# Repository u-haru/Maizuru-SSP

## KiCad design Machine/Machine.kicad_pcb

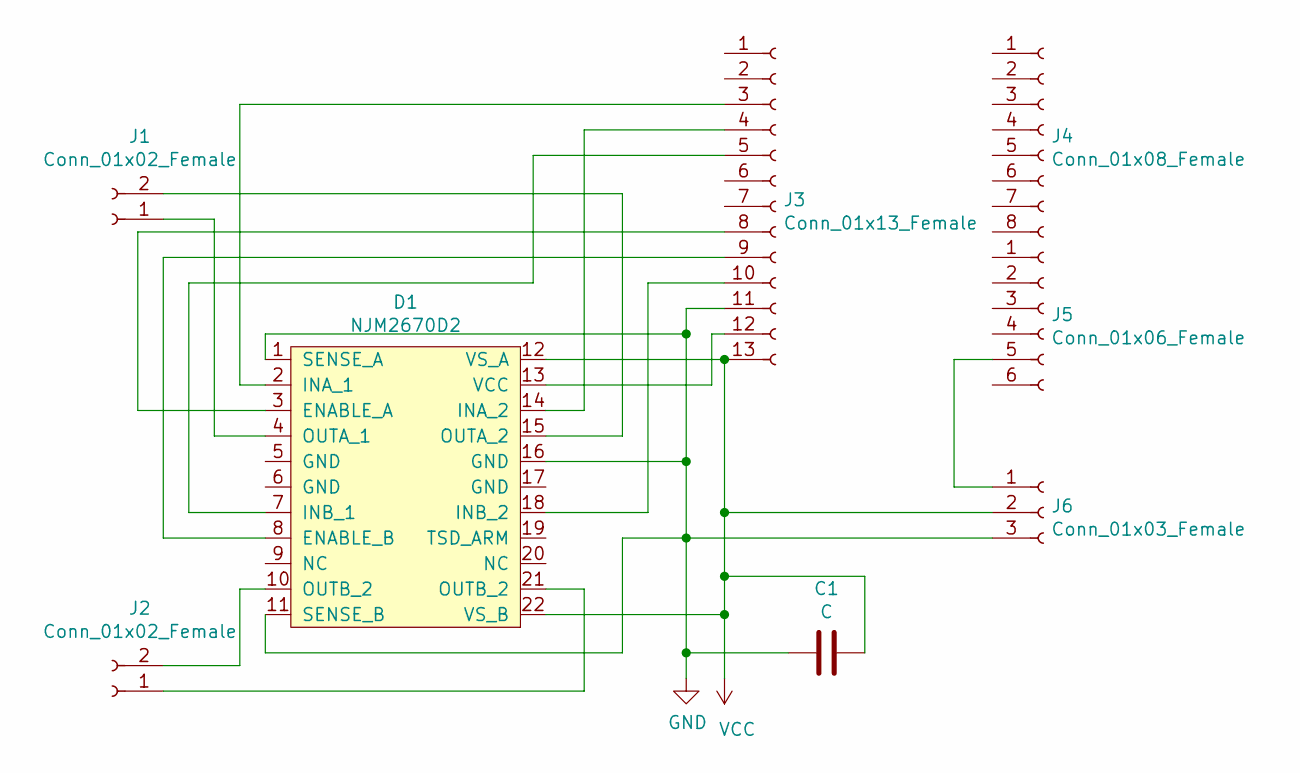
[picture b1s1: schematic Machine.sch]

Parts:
C1: C; C_Disc_D3.0mm_W2.0mm_P2.50mm
D1: NJM2670D2
J1, J2: Conn_01x02_Female; PinSocket_1x02_P2.54mm_Vertical
J3: Conn_01x13_Female; PinSocket_1x13_P2.54mm_Vertical
J4: Conn_01x08_Female; PinSocket_1x08_P2.54mm_Vertical
J5: Conn_01x06_Female; PinSocket_1x06_P2.54mm_Vertical
J6: Conn_01x03_Female; PinSocket_1x03_P2.54mm_Vertical

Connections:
GND: C1.2, D1.1 (SENSE_A), D1.11 (SENSE_B), D1.16 (GND), J3.11, J6.3
unnamed: D1.2 (INA_1), J3.3
unnamed: D1.3 (ENABLE_A), J3.8
unnamed: D1.4 (OUTA_1), J1.1
unnamed: D1.7 (INB_1), J3.5
unnamed: D1.8 (ENABLE_B), J3.9
unnamed: D1.10 (OUTB_2), J2.2
unnamed: D1.13 (VCC), J3.12
unnamed: D1.14 (INA_2), J3.4
unnamed: D1.15 (OUTA_2), J1.2
unnamed: D1.18 (INB_2), J3.10
unnamed: D1.21 (OUTB_2), J2.1
unnamed: J5.5, J6.1
VCC: C1.1, D1.12 (VS_A), D1.22 (VS_B), J3.13, J6.2

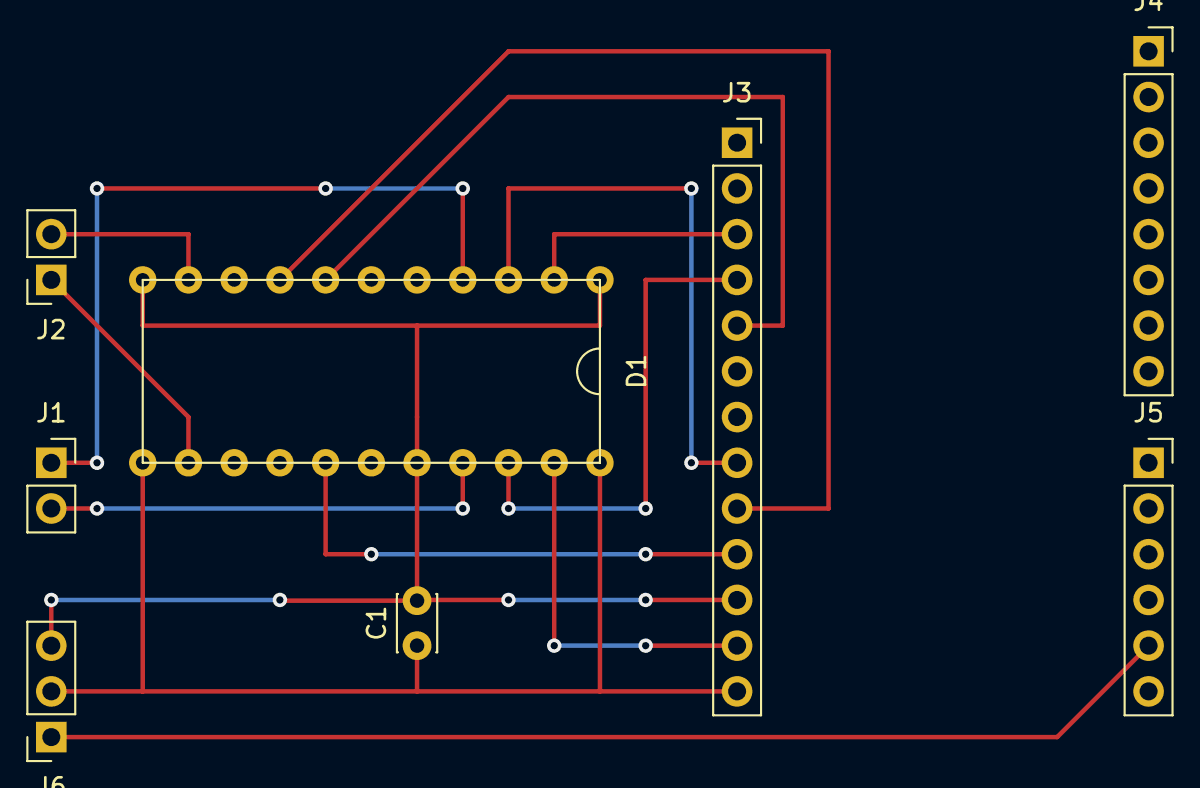
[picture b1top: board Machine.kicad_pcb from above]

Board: 2 copper layers, 8 parts (0 on the bottom side), 14 nets.
